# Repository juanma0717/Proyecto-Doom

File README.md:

# Proyecto-Doom

Uno de los mejores juegos de la historia al alcance de tu mano

¿Estas preparado?

# Integrantes
- Juan Manuel Berdugo Torres
- Fabian Camilo Arciniegas Morales
- Santiago Camargo Molina

# Introducción
El proceso de crear tu propia consola de videojuegos puede parecer abrumador, especialmente si no cuentas con los conocimientos técnicos necesarios. A menudo, esto nos lleva a optar por comprar consolas comerciales, aunque resulten costosas. Con esto en mente, hemos desarrollado un proyecto que te permite diseñar y fabricar tu propia consola estilo Gameboy. No solo aprenderás durante el proceso, sino que también podrás disfrutar del icónico juego DOOM en una consola completamente funcional creada por ti mismo. Este proyecto DIY es altamente escalable, lo que significa que puedes agregar más funciones a la consola, limitadas únicamente por tu imaginación.

# Objetivos
Se definieron diferentes objetivos para plantear el rumbo del proyecto.
## Objetivo general
Diseñar y construir un prototipo electrónico funcional que permita a los usuarios interactuar con el dispositivo de manera fluida y divertida.
## Objetivo especificos
- Desarrollar un circuito electrónico eficiente que controle los elementos del juego.
- Programar el sistema del juego utilizando el lenguaje Micro Python para gestionar las interacciones entre el jugador y el prototipo.

# Alcance
El proyecto implica diseñar y fabricar una consola portátil estilo Gameboy que ejecute DOOM. Se utilizarán componentes como un microcontrolador (ESP32), pantalla, botones y batería, junto con librerías como ST7735 para adaptar el juego. La consola será portátil, con controles básicos y batería recargable, permitiendo la posibilidad de añadir futuras mejoras.

# Resultados
En primer lugar, en términos de ensamblaje, se logró que la pantalla SPI de 1.4 pulgadas mostrara información. Además, se conectaron los pulsadores al ESP32, permitiendo su uso como controles del juego. Con el módulo MH-CD14, se consiguió que todo el circuito funcionara a través de una batería, y finalmente, se añadió un buzzer que mejoró la experiencia al reproducir música.

Sin embargo, en el aspecto del software, no se logró que el juego DOOM funcionara con los diferentes componentes. Hubo un problema de compatibilidad entre los controladores de la pantalla y la librería del juego, ya que estaban en lenguajes de programación diferentes, y hacer que funcionaran juntos excedía el tiempo previsto. Por ello, se decidió optar por hacer funcionar el juego Snake.

# Video

# Conclusiones
En primer lugar, se concluye que ejecutar el juego DOOM en una ESP32 presenta dificultades debido a la complejidad de su código. Aunque existen proyectos documentados previamente, muchos no están en MicroPython o presentan documentación inconsistente.

Por otro lado, el proceso de diseñar una consola resulta muy entretenido, y desarrollar un circuito para ejecutar un juego popular puede atraer a más personas al mundo de la electrónica.

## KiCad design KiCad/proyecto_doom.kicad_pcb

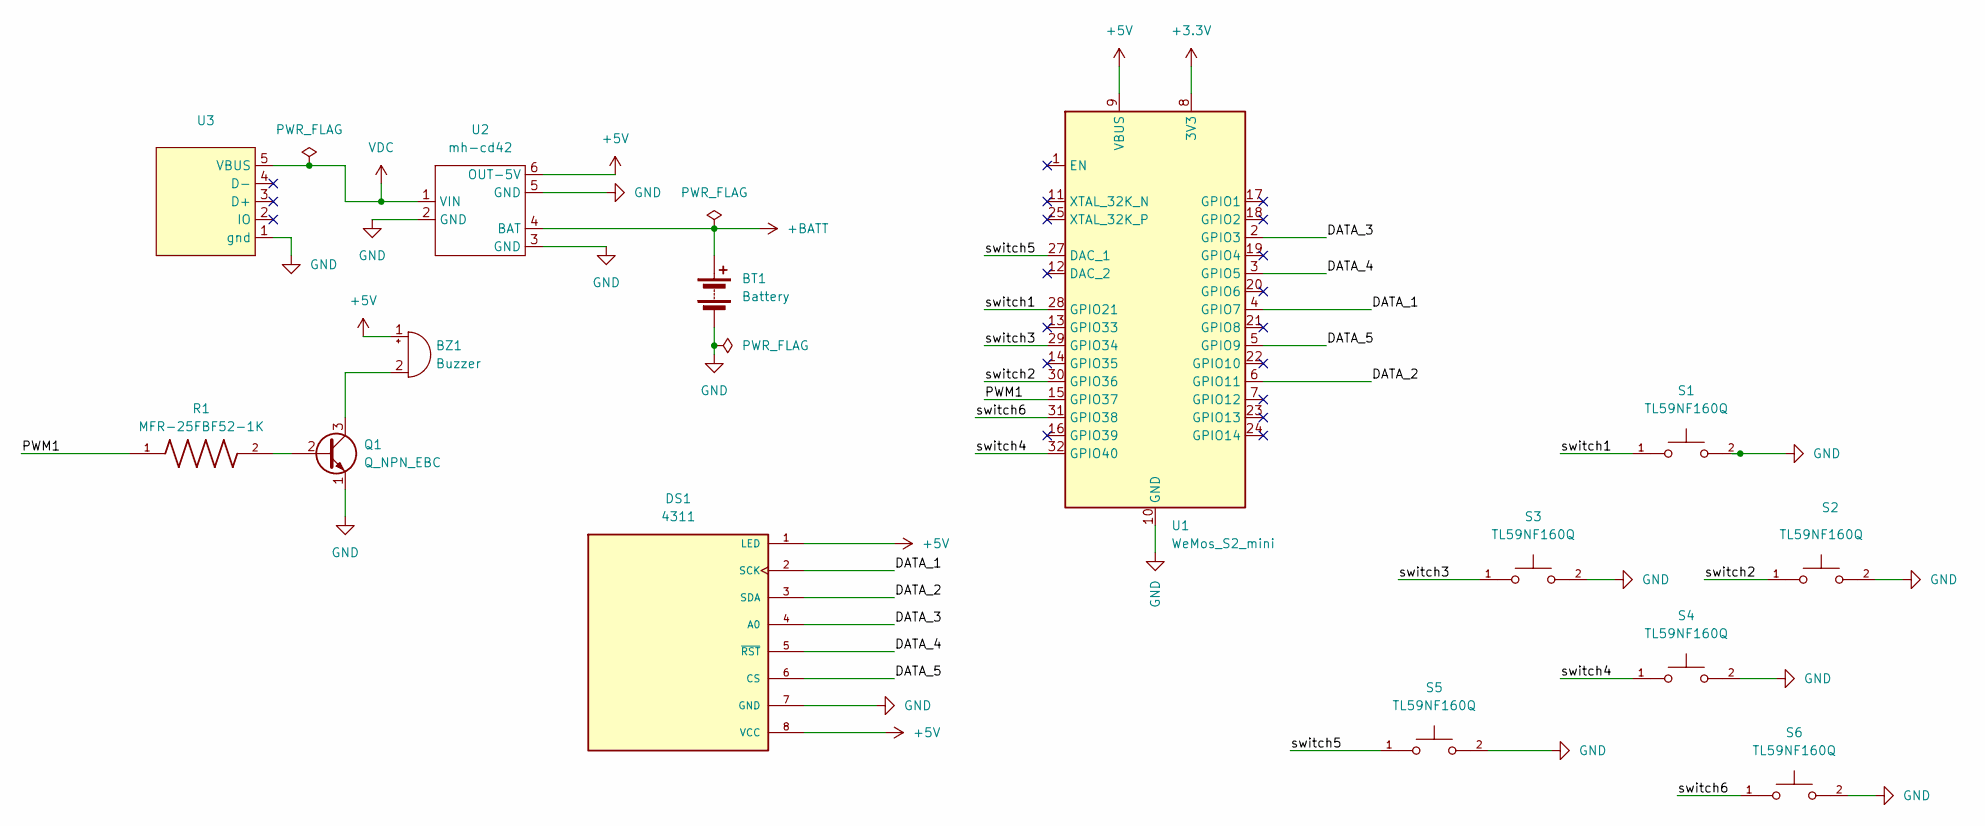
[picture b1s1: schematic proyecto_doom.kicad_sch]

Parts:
BT1: Battery; BatteryHolder_MPD_BH-18650-PC2
BZ1: Buzzer; Buzzer_12x9.5RM7.6
DS1: 4311; tft-spi-1280x160
Q1: Q_NPN_EBC; TO-92
R1: MFR-25FBF52-1K; RESAD1100W55L680D260; PARTREV 201304
S1, S2, S3, S4, S5, S6: TL59NF160Q; SW_TL59NF160Q; PARTREV G
U1: WeMos_S2_mini; WEMOS_S2_mini
U2: mh-cd42
U3: microusb

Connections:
+3.3V: U1.8 (3V3)
+5V: BZ1.1 (+), DS1.1 (LED), DS1.8 (VCC), U1.9 (VBUS), U2.6 (OUT-5V)
+BATT: BT1.1 (+), U2.4 (BAT)
/DATA_1: DS1.2 (SCK), U1.4 (GPIO7)
/DATA_2: DS1.3 (SDA), U1.6 (GPIO11)
/DATA_3: DS1.4 (A0), U1.2 (GPIO3)
/DATA_4: DS1.5 (~RST), U1.3 (GPIO5)
/DATA_5: DS1.6 (CS), U1.5 (GPIO9)
/PWM1: R1.1, U1.15 (GPIO37)
/switch1: S1.1, U1.28 (GPIO21)
/switch2: S2.1, U1.30 (GPIO36)
/switch3: S3.1, U1.29 (GPIO34)
/switch4: S4.1, U1.32 (GPIO40)
/switch5: S5.1, U1.27 (DAC_1)
/switch6: S6.1, U1.31 (GPIO38)
GND: BT1.2 (-), DS1.7 (GND), Q1.1 (E), S1.2, S2.2, S3.2, S4.2, S5.2, S6.2, U1.10 (GND), U1.26 (GND), U2.2 (GND), U2.3 (GND), U2.5 (GND), U3.1 (gnd)
unnamed: BZ1.2 (-), Q1.3 (C)
unnamed: Q1.2 (B), R1.2
VDC: U2.1 (VIN), U3.5 (VBUS)

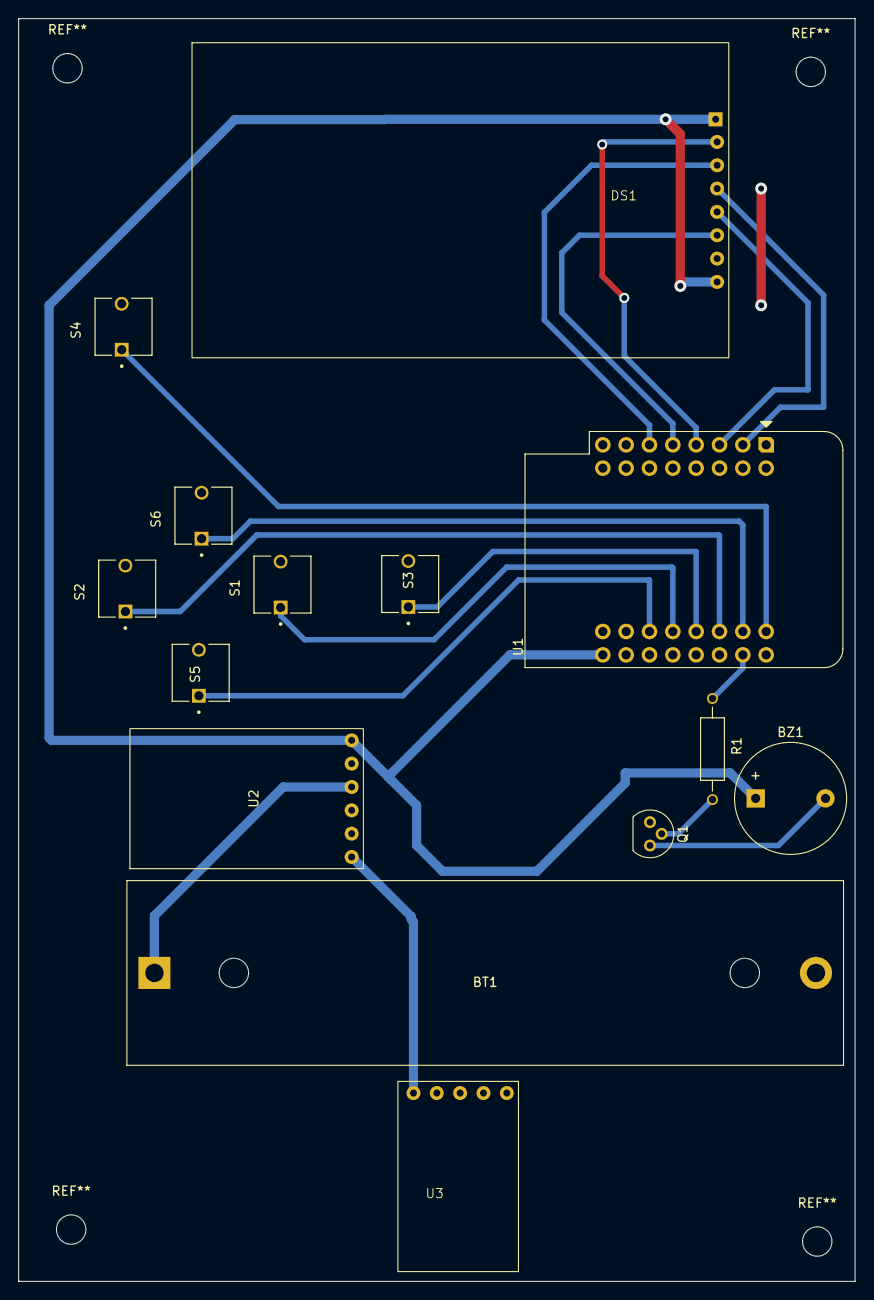
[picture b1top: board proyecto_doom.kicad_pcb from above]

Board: 2 copper layers, 91.0 x 137.4 mm, 14 parts (0 on the bottom side), 18 nets.

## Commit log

2024-09-25 Create KiCad librerias
2024-09-25 Create KiCad_librerias
2024-09-25 Rename 20240828_105800.jpg to img_prot_final.jpg
2024-09-25 Rename img_prot_final.jpg to img_prot_buzzer.jpg
2024-09-25 Rename 20240828_114020.jpg to img_prot_superior.jpg
2024-09-25 Rename 20240828_114310.jpg to img_prot_frontal.jpg
2024-09-25 Rename 20240828_114318.jpg to img_prot_trasero.jpg
2024-09-25 Rename 20240918_130012.jpg to img_prot_final.jpg
2024-09-25 Rename 20240918_130012.jpg to img_proyec_final.jpg
